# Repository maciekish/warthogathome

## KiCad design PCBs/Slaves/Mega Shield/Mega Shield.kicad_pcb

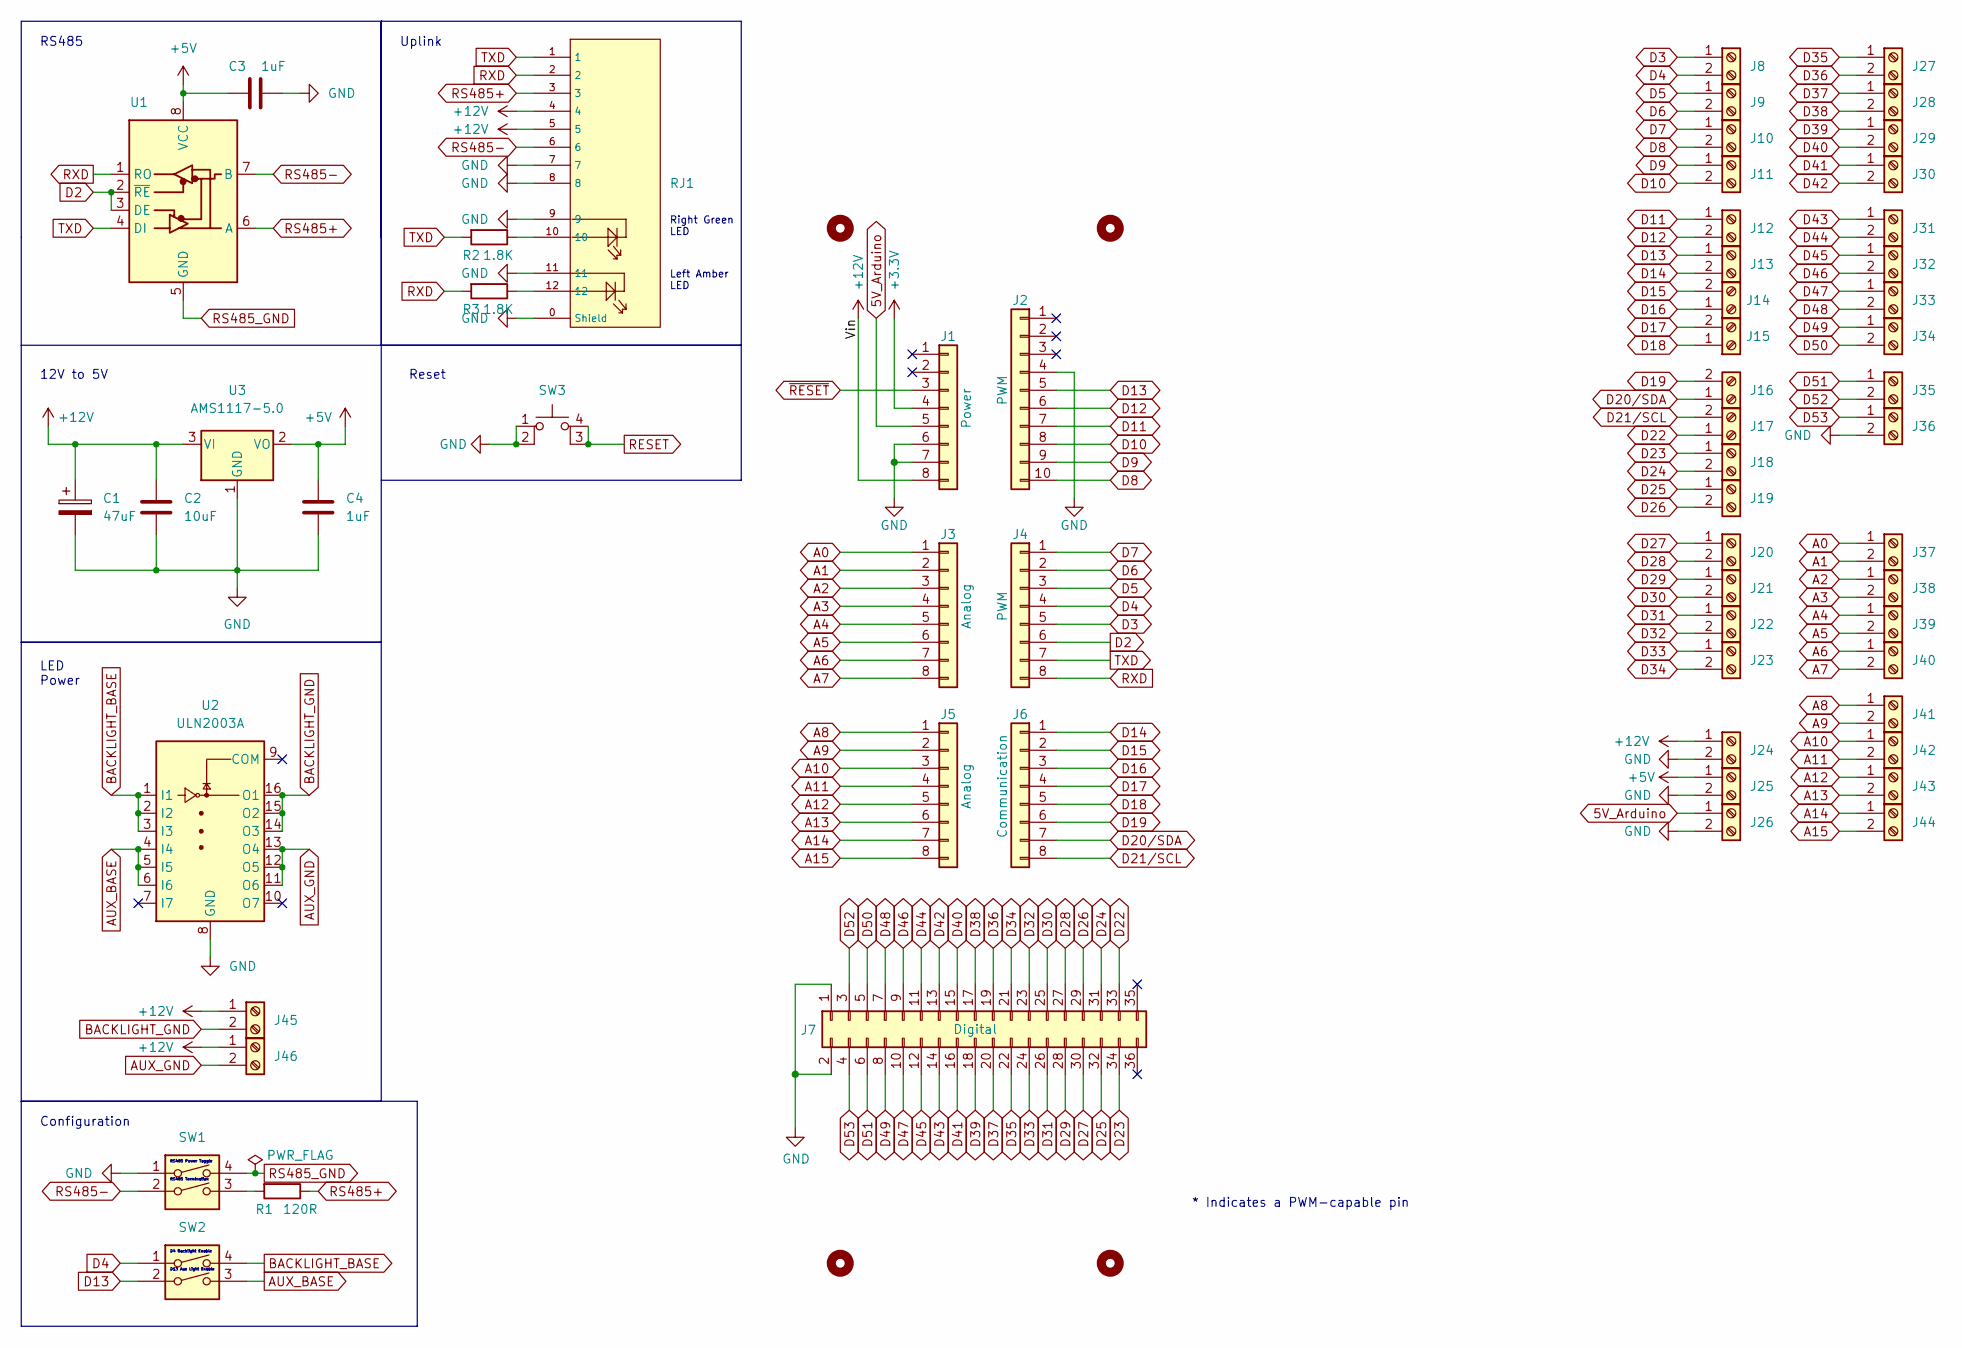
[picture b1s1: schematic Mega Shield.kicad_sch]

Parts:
C1: 47uF; CP_Elec_5x5.4; LCSC C96178
C2: 10uF; C0402; LCSC C15525
C3, C4: 1uF; C0402; LCSC C52923
H1, H2, H3, H4: MountingHole; MountingHole_3.2mm_M3
J1: Power; PinSocket_1x08_P2.54mm_Vertical
J2: PWM; PinSocket_1x10_P2.54mm_Vertical
J3, J5: Analog; PinSocket_1x08_P2.54mm_Vertical
J4: PWM; PinSocket_1x08_P2.54mm_Vertical
J6: Communication; PinSocket_1x08_P2.54mm_Vertical
J7: Digital; PinSocket_2x18_P2.54mm_Vertical
J8, J9, J10, J11, J12, J13, J14, J15, J16, J17, J18, J19, J20, J21, J22, J23, J24, J25, J26, J27, J28, J29, J30, J31, J32, J33, J34, J35, J36, J37, J38, J39, J40, J41, J42, J43, J44, J45, J46: Screw_Terminal_01x02; CONN-TH_WJ126V-5.0-2P; LCSC C557685
R1: 120R; R_0805_2012Metric; LCSC C17437
R2, R3: 1.8K; R_0805_2012Metric; LCSC C17398
RJ1: RJ45-B-1*1; RJ45-TH_B-1-1; LCSC C138392
SW1, SW2: SW_DIP_x02; SW-SMD_DSHP02TSGER; LCSC C367376
SW3: SW_MEC_5E; SW-SMD_4P-L5.1-W5.1-P3.70-LS6.5-TL-2; LCSC C318884
U1: MAX487ESA+T; SOIC-8_L5.0-W4.0-P1.27-LS6.0-BL; LCSC C9953
U2: ULN2003A; SOP-16_L10.0-W3.9-P1.27-LS6.0-BL; LCSC C7512
U3: AMS1117-5.0; SOT-223-3_TabPin2; LCSC C6187

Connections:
5V_Arduino: J1.5, J26.1
+3V3: J1.4
+5V: C3.1, C4.1, J25.1, U1.8 (VCC), U3.2 (VO)
+12V: C1.1, C2.1, J1.8, J24.1, J45.1, J46.1, RJ1.4, RJ1.5, U3.3 (VI)
A0: J3.1, J37.1
A1: J3.2, J37.2
A2: J3.3, J38.1
A3: J3.4, J38.2
A4: J3.5, J39.1
A5: J3.6, J39.2
A6: J3.7, J40.1
A7: J3.8, J40.2
A8: J5.1, J41.1
A9: J5.2, J41.2
A10: J5.3, J42.1
A11: J5.4, J42.2
A12: J5.5, J43.1
A13: J5.6, J43.2
A14: J5.7, J44.1
A15: J5.8, J44.2
AUX_BASE: SW2.3, U2.4 (I4), U2.5 (I5), U2.6 (I6)
AUX_GND: J46.2, U2.11 (O6), U2.12 (O5), U2.13 (O4)
BACKLIGHT_BASE: SW2.4, U2.1 (I1), U2.2 (I2), U2.3 (I3)
BACKLIGHT_GND: J45.2, U2.14 (O3), U2.15 (O2), U2.16 (O1)
D2: J4.6, U1.2 (~RE), U1.3 (DE)
D3: J4.5, J8.1
D4: J4.4, J8.2, SW2.1
D5: J4.3, J9.1
D6: J4.2, J9.2
D7: J4.1, J10.1
D8: J2.10, J10.2
D9: J2.9, J11.1
D10: J2.8, J11.2
D11: J2.7, J12.1
D12: J2.6, J12.2
D13: J2.5, J13.1, SW2.2
D14: J6.1, J13.2
D15: J6.2, J14.2
D16: J6.3, J14.1
D17: J6.4, J15.2
D18: J6.5, J15.1
D19: J6.6, J16.2
D20/SDA: J6.7, J16.1
D21/SCL: J6.8, J17.2
D22: J7.33, J17.1
D23: J7.34, J18.1
D24: J7.31, J18.2
D25: J7.32, J19.1
D26: J7.29, J19.2
D27: J7.30, J20.1
D28: J7.27, J20.2
D29: J7.28, J21.1
D30: J7.25, J21.2
D31: J7.26, J22.1
D32: J7.23, J22.2
D33: J7.24, J23.1
D34: J7.21, J23.2
D35: J7.22, J27.1
D36: J7.19, J27.2
D37: J7.20, J28.1
D38: J7.17, J28.2
D39: J7.18, J29.1
D40: J7.15, J29.2
D41: J7.16, J30.1
D42: J7.13, J30.2
D43: J7.14, J31.1
D44: J7.11, J31.2
D45: J7.12, J32.1
D46: J7.9, J32.2
D47: J7.10, J33.1
D48: J7.7, J33.2
D49: J7.8, J34.1
D50: J7.5, J34.2
D51: J7.6, J35.1
D52: J7.3, J35.2
D53: J7.4, J36.1
GND: C1.2, C2.2, C3.2, C4.2, J1.6, J1.7, J2.4, J7.1, J7.2, J24.2, J25.2, J26.2, J36.2, RJ1.0 (Shield), RJ1.7, RJ1.8, RJ1.9, RJ1.11, SW1.1, SW3.1, SW3.2, U2.8 (GND), U3.1 (GND)
unnamed: R1.2, SW1.3
unnamed: R2.1, RJ1.10
unnamed: R3.1, RJ1.12
RESET: SW3.3 (K), SW3.4 (A)
RS485+: R1.1, RJ1.3, U1.6 (A)
RS485-: RJ1.6, SW1.2, U1.7 (B)
RS485_GND: SW1.4, U1.5 (GND)
RXD: J4.8, R3.2, RJ1.2, U1.1 (RO)
TXD: J4.7, R2.2, RJ1.1, U1.4 (DI)
~RESET: J1.3

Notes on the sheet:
Uplink
12V to 5V
D4 Backlight Enable
RS485 Power Toggle
Right Green LED
D13 Aux Light Enable
Reset
RS485
Configuration
RS485 Termination
* Indicates a PWM-capable pin
LED Power
Left Amber LED

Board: 2 copper layers, 70 parts (0 on the bottom side), 85 nets, no tracks yet.

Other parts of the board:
MH1, MH2, MH3, MH4, MH5, MH6: MountingHole_3.2mm

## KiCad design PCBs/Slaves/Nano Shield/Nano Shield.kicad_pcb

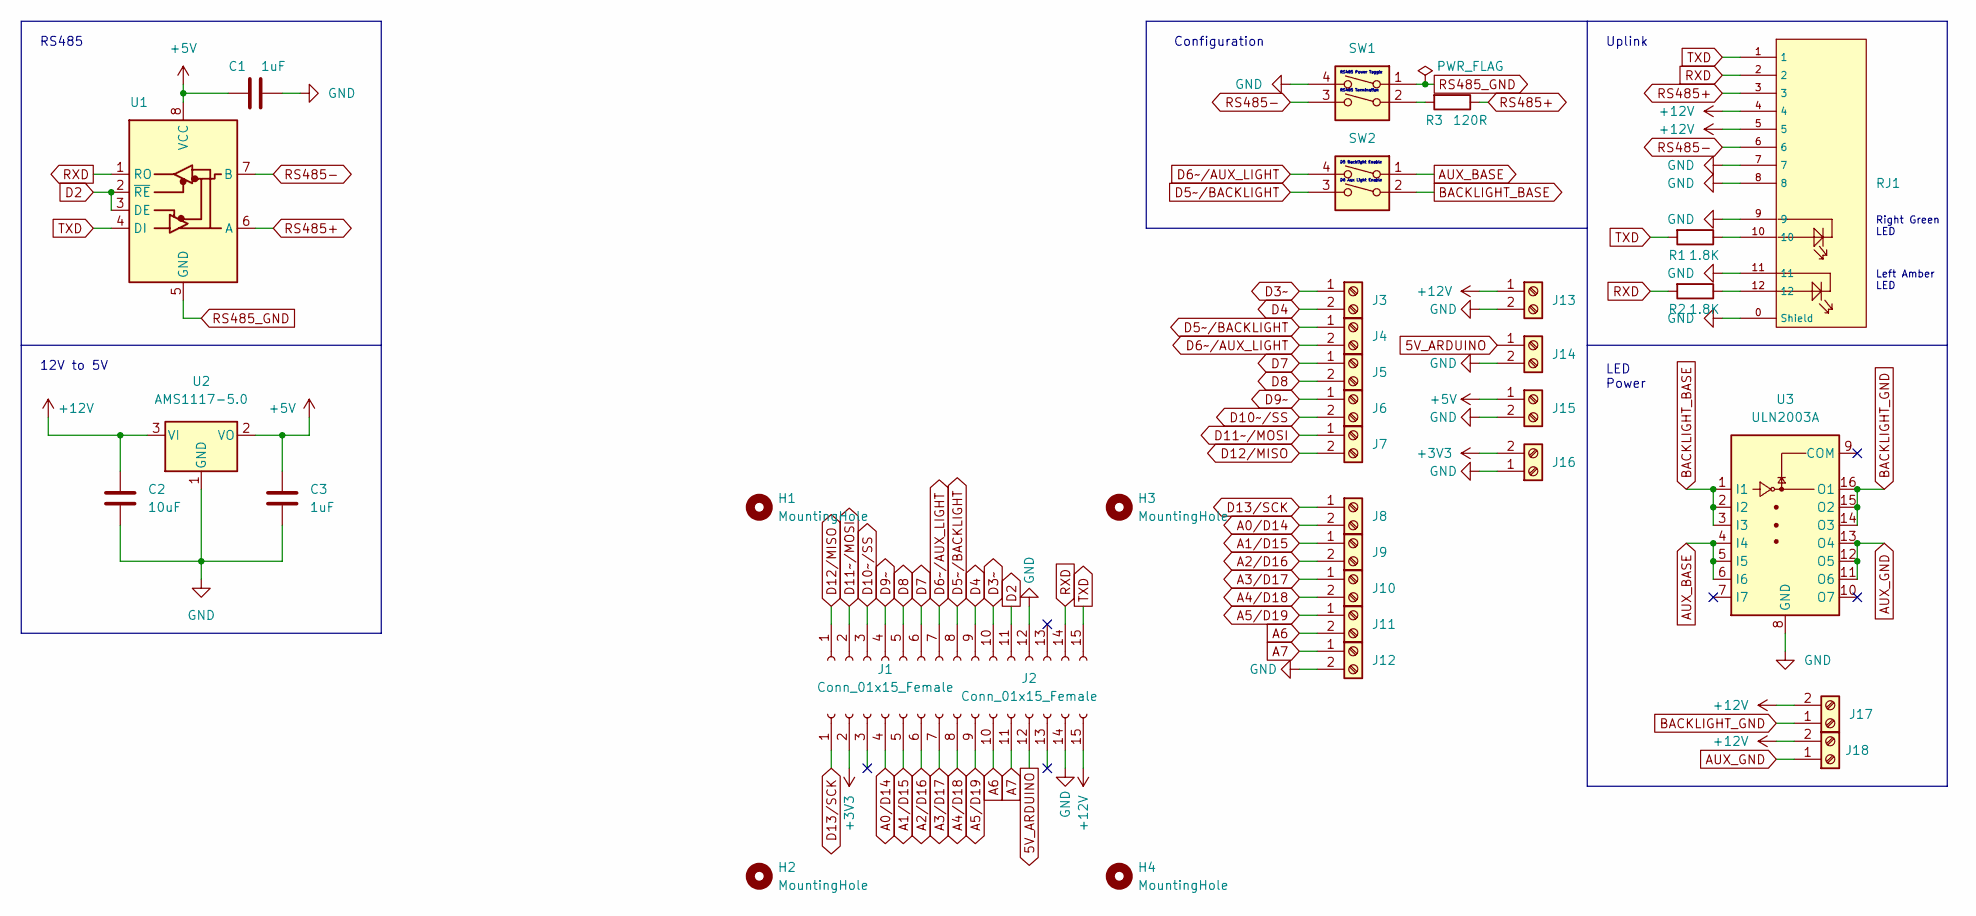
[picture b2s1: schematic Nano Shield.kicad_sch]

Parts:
C1, C3: 1uF; C0402; LCSC C52923
C2: 10uF; C0402; LCSC C15525
H1, H2, H3, H4: MountingHole; MountingHole_3.2mm_M3
J1, J2: Conn_01x15_Female; PinSocket_1x15_P2.54mm_Vertical
J3, J4, J5, J6, J7, J8, J9, J10, J11, J12, J13, J14, J15, J16, J17, J18: Screw_Terminal_01x02; CONN-TH_WJ126V-5.0-2P; LCSC C557685
R1, R2: 1.8K; R_0805_2012Metric; LCSC C17398
R3: 120R; R_0805_2012Metric; LCSC C17437
RJ1: RJ45-B-1*1; RJ45-TH_B-1-1; LCSC C138392
SW1, SW2: SW_DIP_x02; SW-SMD_DSHP02TSGER; LCSC C367376
U1: MAX487ESA+T; SOIC-8_L5.0-W4.0-P1.27-LS6.0-BL; LCSC C9953
U2: AMS1117-5.0; SOT-223-3_TabPin2; LCSC C6187
U3: ULN2003A; SOP-16_L10.0-W3.9-P1.27-LS6.0-BL; LCSC C7512

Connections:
5V_ARDUINO: J2.12, J14.1
+3V3: J2.2, J16.2
+5V: C1.1, C3.1, J15.1, U1.8 (VCC), U2.2 (VO)
+12V: C2.1, J2.15, J13.1, J17.2, J18.2, RJ1.4, RJ1.5, U2.3 (VI)
A0/D14: J2.4, J8.2
A1/D15: J2.5, J9.1
A2/D16: J2.6, J9.2
A3/D17: J2.7, J10.1
A4/D18: J2.8, J10.2
A5/D19: J2.9, J11.1
A6: J2.10, J11.2
A7: J2.11, J12.1
AUX_BASE: SW2.1, U3.4 (I4), U3.5 (I5), U3.6 (I6)
AUX_GND: J18.1, U3.11 (O6), U3.12 (O5), U3.13 (O4)
BACKLIGHT_BASE: SW2.2, U3.1 (I1), U3.2 (I2), U3.3 (I3)
BACKLIGHT_GND: J17.1, U3.14 (O3), U3.15 (O2), U3.16 (O1)
D2: J1.11, U1.2 (~RE), U1.3 (DE)
D3~: J1.10, J3.1
D4: J1.9, J3.2
D5~/BACKLIGHT: J1.8, J4.1, SW2.3
D6~/AUX_LIGHT: J1.7, J4.2, SW2.4
D7: J1.6, J5.1
D8: J1.5, J5.2
D9~: J1.4, J6.1
D10~/SS: J1.3, J6.2
D11~/MOSI: J1.2, J7.1
D12/MISO: J1.1, J7.2
D13/SCK: J2.1, J8.1
GND: C1.2, C2.2, C3.2, J1.12, J2.14, J12.2, J13.2, J14.2, J15.2, J16.1, RJ1.0 (Shield), RJ1.7, RJ1.8, RJ1.9, RJ1.11, SW1.4, U2.1 (GND), U3.8 (GND)
unnamed: R1.1, RJ1.10
unnamed: R2.1, RJ1.12
unnamed: R3.2, SW1.2
RS485+: R3.1, RJ1.3, U1.6 (A)
RS485-: RJ1.6, SW1.3, U1.7 (B)
RS485_GND: SW1.1, U1.5 (GND)
RXD: J1.14, R2.2, RJ1.2, U1.1 (RO)
TXD: J1.15, R1.2, RJ1.1, U1.4 (DI)

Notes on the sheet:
D5 Backlight Enable
LED Power
Right Green LED
RS485 Power Toggle
Uplink
12V to 5V
D6 Aux Light Enable
Left Amber LED
RS485 Termination
Configuration
RS485

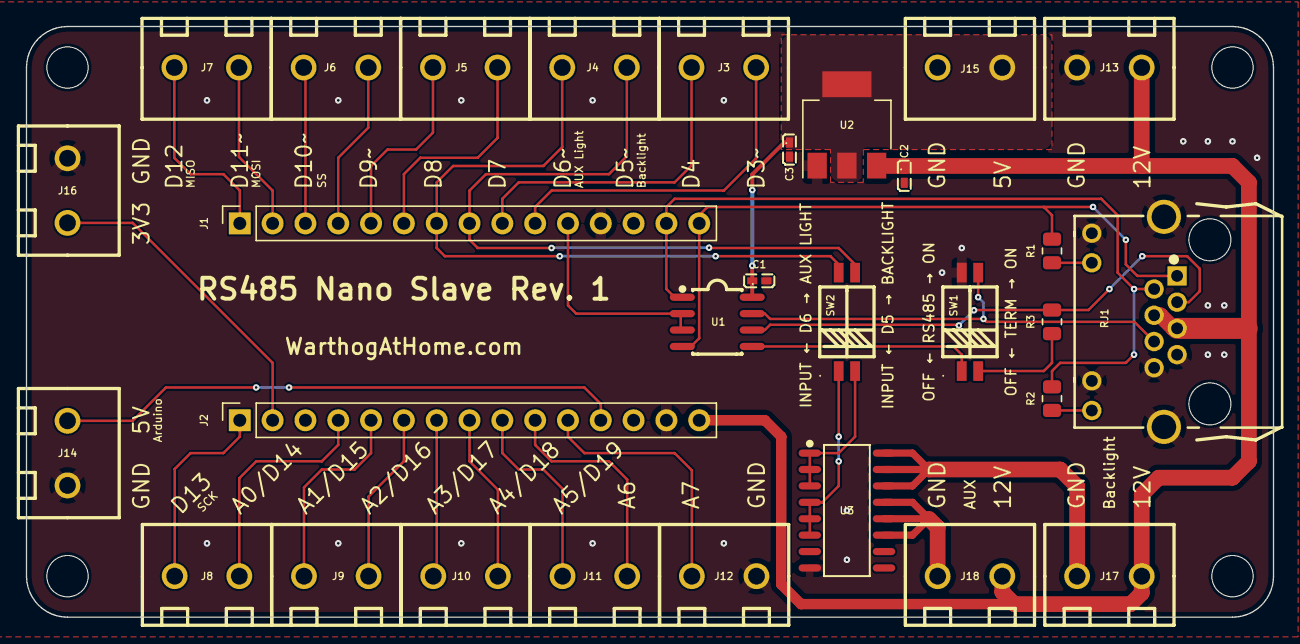
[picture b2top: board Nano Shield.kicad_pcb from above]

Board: 2 copper layers, 96.5 x 45.7 mm, 34 parts (0 on the bottom side), 37 nets.
